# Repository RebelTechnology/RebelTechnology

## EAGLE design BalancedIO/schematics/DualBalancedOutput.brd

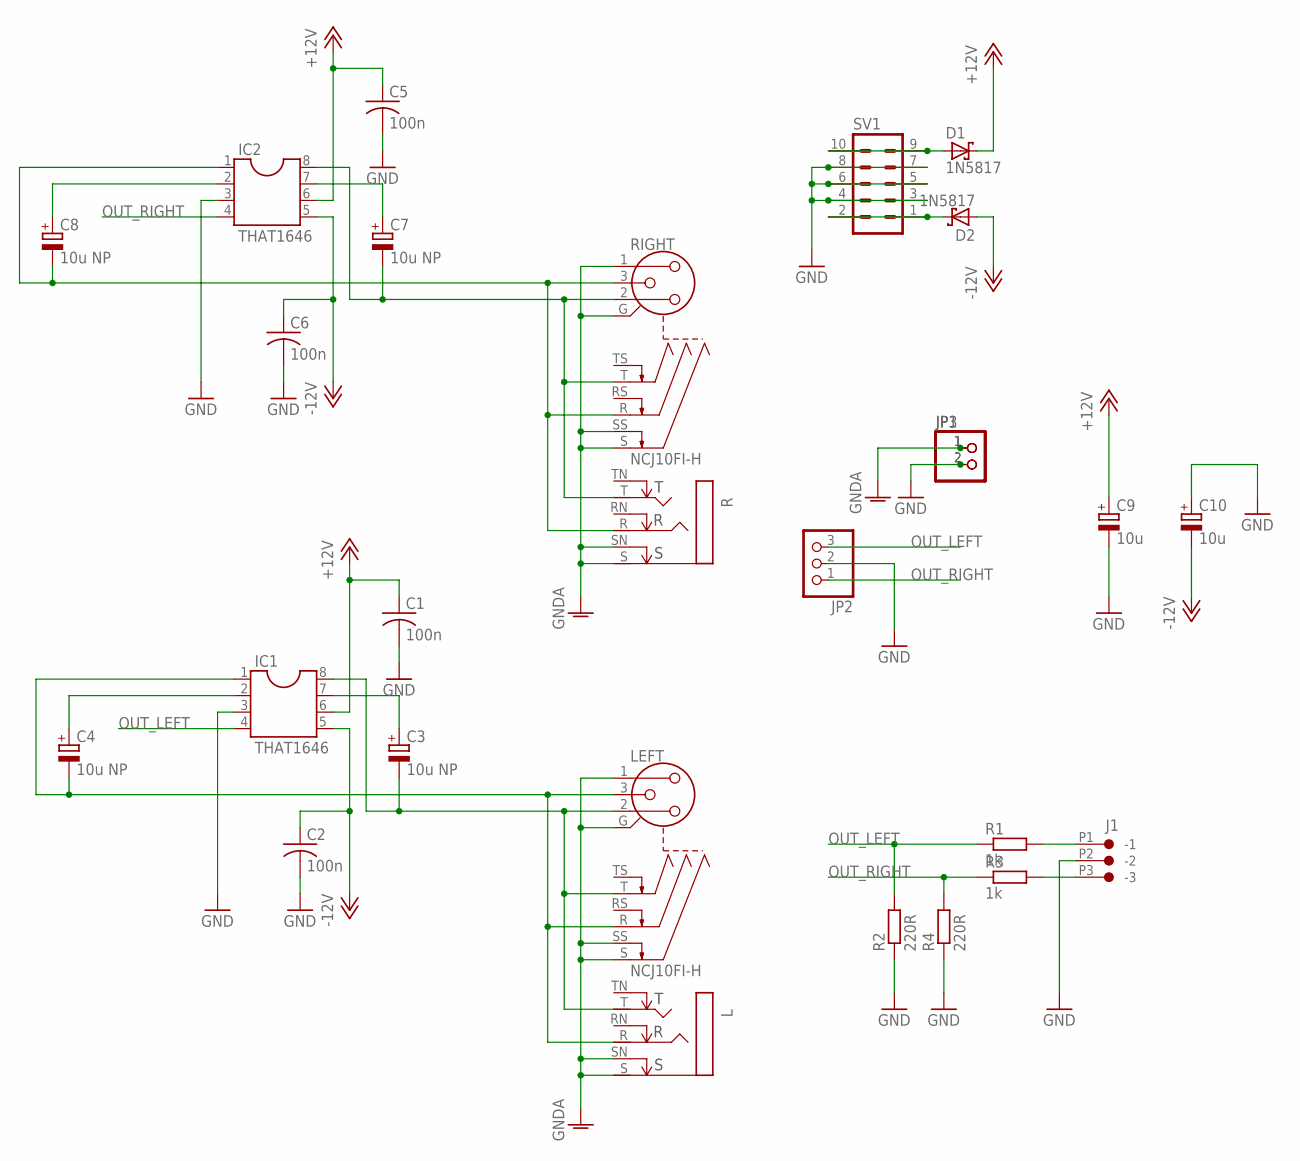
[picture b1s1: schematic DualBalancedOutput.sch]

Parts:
C1, C2, C5, C6: 100n; C050-024X044
C3, C4, C7, C8: 10u NP; E2-5
C9, C10: 10u; E5-6
D1, D2: 1N5817; DO41-7.6
IC1, IC2: THAT1646; DIL08
J1: CON-JST_PH_3W
JP1, JP3: PINHD-1X2; 1X02
JP2: PINHD-1X3; 1X03
L: NEUTRIK_NMJ6HCD2; NMJ6HCD2
LEFT: NCJ10FI-H
R: NEUTRIK_NMJ6HCD2; NMJ6HCD2
R1, R3: 1k; 0204/7
R2, R4: 220R; 0204/7
RIGHT: NCJ10FI-H
SV1: MA05-2

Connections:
+12V: C1.1, C5.1, C9.+, D1.C, IC1.6, IC2.6
-12V: C2.1, C6.1, C10.-, D2.A, IC1.5, IC2.5
GND: C1.2, C2.2, C5.2, C6.2, C9.-, C10.+, IC1.3, IC2.3, J1.P2 (-2), JP1.2, JP2.2, JP3.2, R2.1, R4.1, SV1.3, SV1.4, SV1.5, SV1.6, SV1.7, SV1.8
GNDA: JP1.1, JP3.1, L.S, L.SN, LEFT.1, LEFT.G, LEFT.S, LEFT.SS, R.S, R.SN, RIGHT.1, RIGHT.G, RIGHT.S, RIGHT.SS
unnamed: C3.-, IC1.8, L.T, LEFT.2, LEFT.T
unnamed: C4.-, IC1.1, L.R, LEFT.3, LEFT.R
unnamed: C3.+, IC1.7
unnamed: C4.+, IC1.2
unnamed: D2.C, SV1.1, SV1.2
unnamed: D1.A, SV1.9, SV1.10
unnamed: J1.P3 (-3), R3.2
unnamed: C7.+, IC2.7
unnamed: J1.P1 (-1), R1.2
unnamed: C8.+, IC2.2
unnamed: C7.-, IC2.8, R.T, RIGHT.2, RIGHT.T
unnamed: C8.-, IC2.1, R.R, RIGHT.3, RIGHT.R
OUT_LEFT: IC1.4, JP2.3, R1.1, R2.2
OUT_RIGHT: IC2.4, JP2.1, R3.1, R4.2

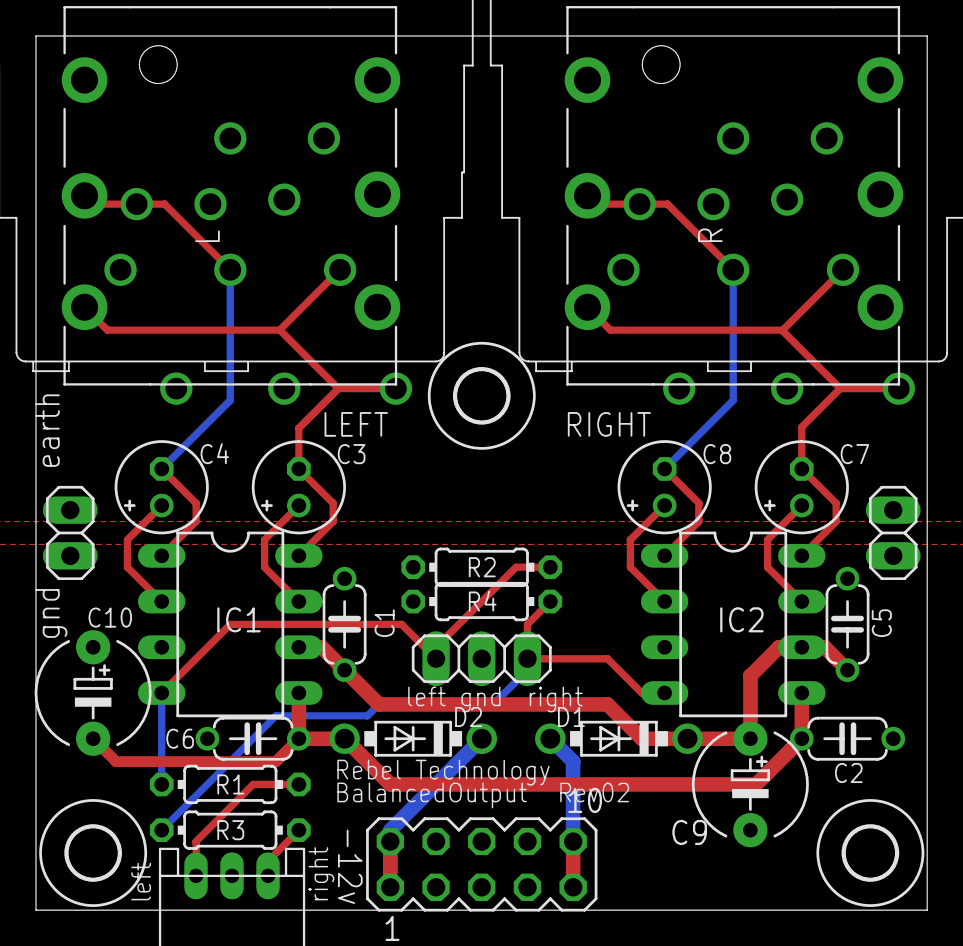
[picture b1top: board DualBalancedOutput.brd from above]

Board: 2 copper layers, 49.5 x 48.6 mm, 30 parts (0 on the bottom side), 18 nets.

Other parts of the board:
U$1, U$2, U$3: 2,8

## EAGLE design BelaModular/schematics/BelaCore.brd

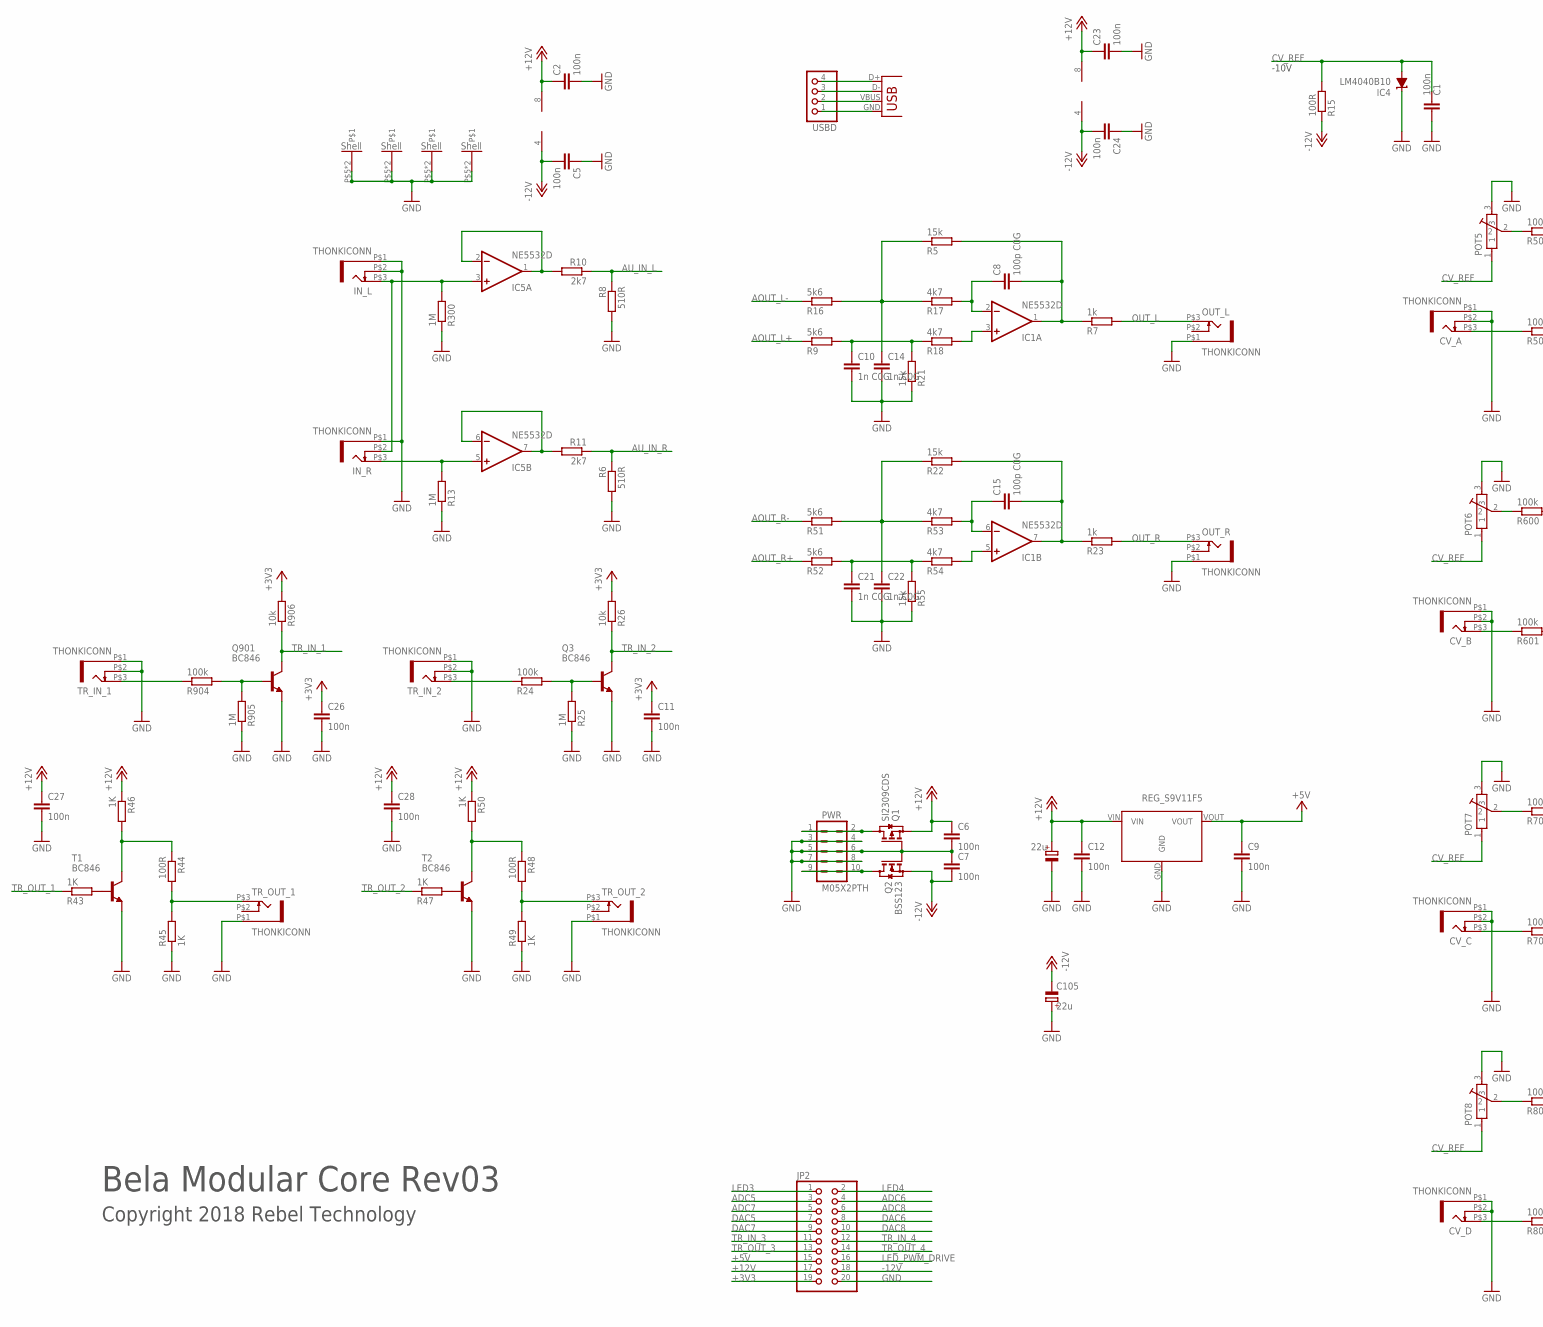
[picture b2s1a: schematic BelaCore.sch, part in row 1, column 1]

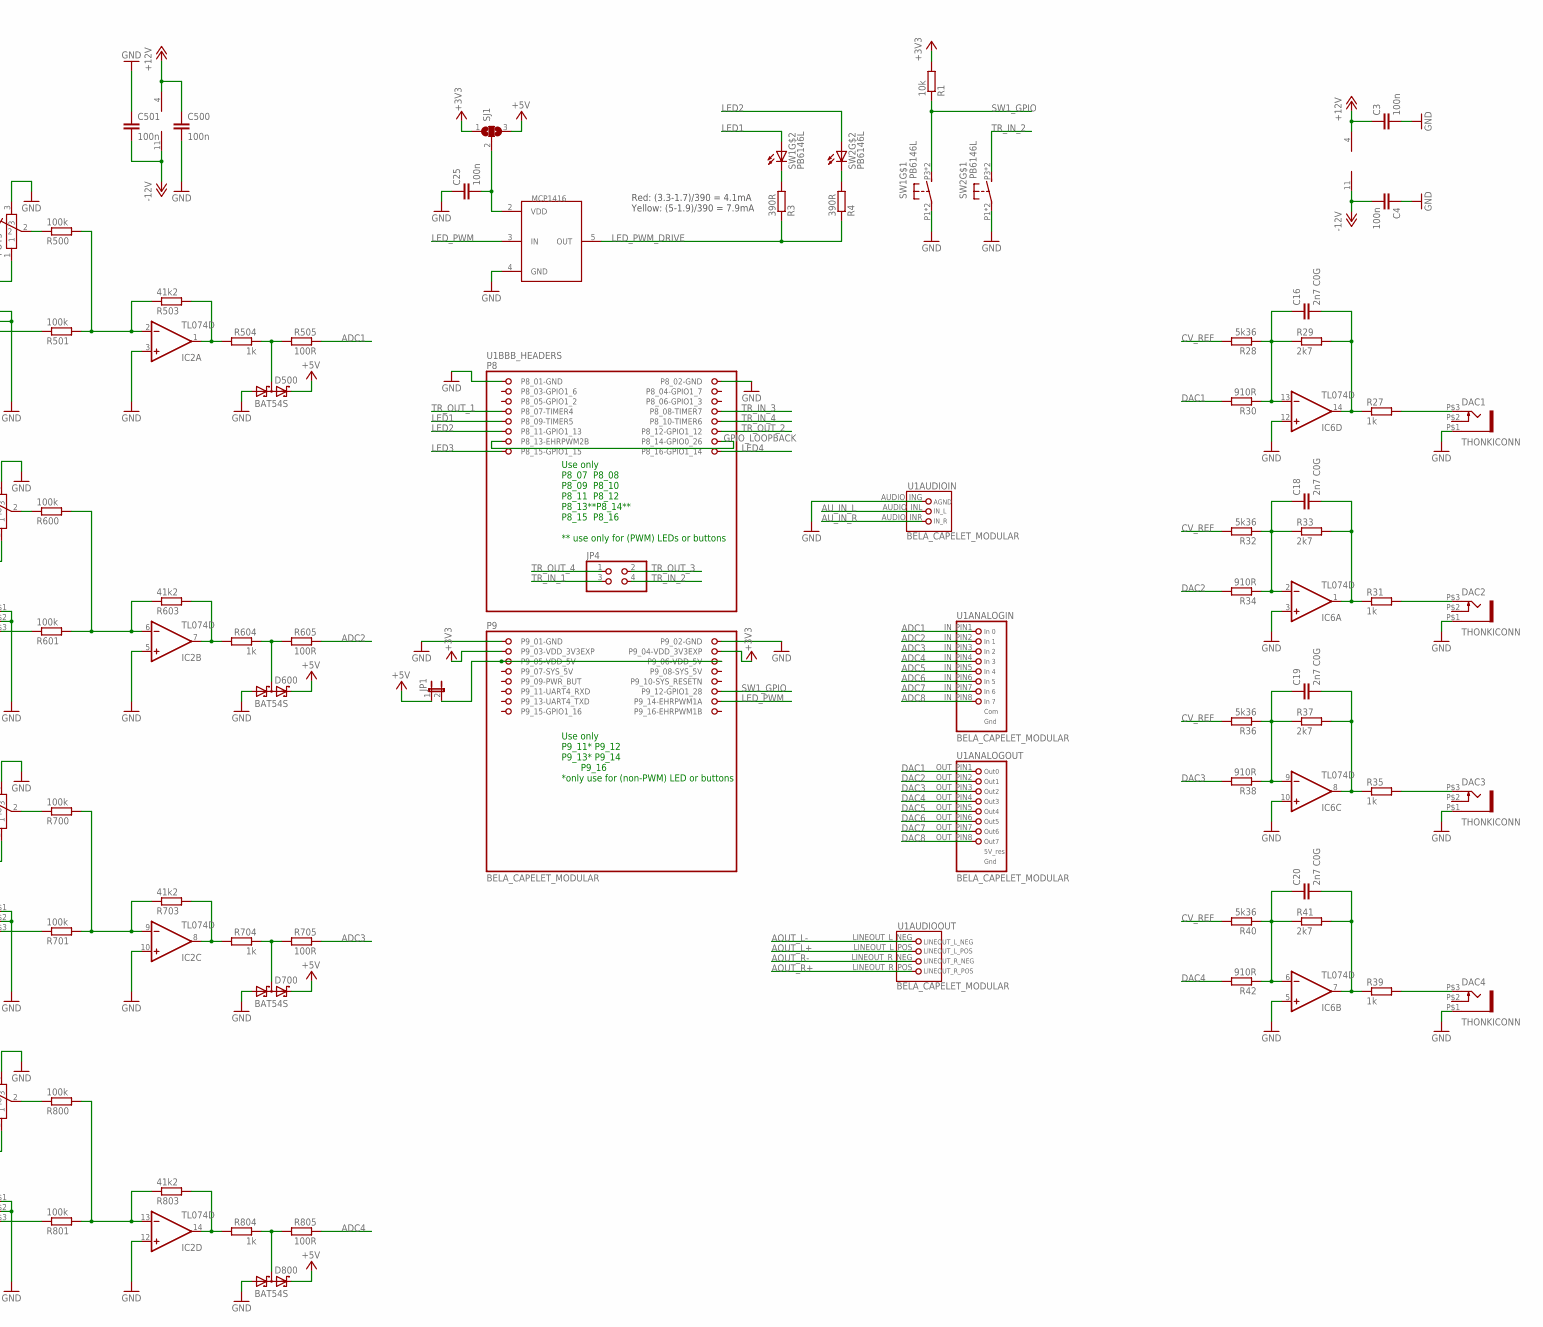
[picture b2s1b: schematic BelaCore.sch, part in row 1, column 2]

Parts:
C1, C2, C3, C4, C5, C6, C7, C9, C11, C12, C23, C24, C25, C26, C27, C28, C500, C501: 100n; C0603
C8, C15: 100p C0G; C0603
C10, C14, C21, C22: 1n C0G; C0603
C16, C18, C19, C20: 2n7 C0G; C0603
C17, C105: 22u; CPOL-5
CV_A: THONKICONN
CV_B: THONKICONN
CV_C: THONKICONN
CV_D: THONKICONN
D500, D600, D700, D800: BAT54S; SOT23
DAC1, DAC2, DAC3, DAC4: THONKICONN
IC1, IC5: NE5532D; SO08
IC2, IC6: TL074D; SO14
IC4: LM4040B10; DBZ_R-PDSO-G3
IN_L: THONKICONN
IN_R: THONKICONN
JP1: JUMPER-2PTH; 1X02
JP2: PINHD-2X10; 2X10
JP4: PINHD-2X02_2.54-SMD; 2X02SMD
OUT_L: THONKICONN
OUT_R: THONKICONN
POT5, POT6, POT7, POT8: POT-ALPS-RK09L1140
PWR: M05X2PTH; AVR_ICSP
Q1: SI2309CDS; SOT23
Q2: BSS123; SOT23
Q3, Q901: BC846; SOT23
R1, R26, R906: 10k; 0603
R3, R4: 390R; 0603
R5, R21, R22, R55: 15k; 0603
R6, R8: 510R; 0603
R7, R23, R27, R31, R35, R39, R504, R604, R704, R804: 1k; 0603
R9, R16, R51, R52: 5k6; 0603
R10, R11, R29, R33, R37, R41: 2k7; 0603
R13, R25, R300, R905: 1M; 0603
R15, R44, R48, R505, R605, R705, R805: 100R; 0603
R17, R18, R53, R54: 4k7; 0603
R24, R500, R501, R600, R601, R700, R701, R800, R801, R904: 100k; 0603
R28, R32, R36, R40: 5k36; 0603
R30, R34, R38, R42: 910R; 0603
R43, R45, R46, R47, R49, R50: 1K; 0603
R503, R603, R703, R803: 41k2; 0603
SJ1: SJ2W; SJ_2
SW1, SW2: PB6146L
T1, T2: BC846; SOT23
TR_IN_1, TR_IN_2: THONKICONN
TR_OUT_1, TR_OUT_2: THONKICONN
U1: BELA_CAPELET_MODULAR
U2: MCP1416; SOT23-5
U3: REG_S9V11F5
USBD: PINHD-1X4; 1X04
X1: USBPTH-VERTICAL; USB-B-PTH-VERTICAL

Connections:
+3V3: C11.1, C26.1, JP2.19, R1.2, R26.2, R906.2, SJ1.1, U1.P9_03 (P9_03-VDD_3V3EXP), U1.P9_04 (P9_04-VDD_3V3EXP)
+5V: C9.1, D500.2 (C2), D600.2 (C2), D700.2 (C2), D800.2 (C2), JP1.1, JP2.15, SJ1.3, U3.VOUT
+12V: C2.1, C3.1, C6.1, C12.1, C17.+, C23.1, C27.1, C28.1, C500.1, IC1.8 (V+), IC2.4 (V+), IC5.8 (V+), IC6.4 (V+), JP2.17, Q1.2 (S), R46.1, R50.1, U3.VIN
-12V: C4.2, C5.2, C7.2, C24.2, C105.-, C501.2, IC1.4 (V-), IC2.11 (V-), IC5.4 (V-), IC6.11 (V-), JP2.18, Q2.2 (S), R15.1
ADC1: R505.1, U1.IN_PIN1 (1)
ADC2: R605.1, U1.IN_PIN2 (2)
ADC3: R705.1, U1.IN_PIN3 (3)
ADC4: R805.1, U1.IN_PIN4 (4)
ADC5: JP2.3, U1.IN_PIN5 (5)
ADC6: JP2.4, U1.IN_PIN6 (6)
ADC7: JP2.5, U1.IN_PIN7 (7)
ADC8: JP2.6, U1.IN_PIN8 (8)
AOUT_L+: R9.1, U1.LINEOUT_L_POS (2)
AOUT_L-: R16.1, U1.LINEOUT_L_NEG (1)
AOUT_R+: R52.1, U1.LINEOUT_R_POS (4)
AOUT_R-: R51.1, U1.LINEOUT_R_NEG (3)
AU_IN_L: R8.1, R10.1, U1.AUDIO_INL (2)
AU_IN_R: R6.1, R11.1, U1.AUDIO_INR (3)
CV_REF: C1.1, IC4.2 (A), POT5.1, POT6.1, POT7.1, POT8.1, R15.2, R28.2, R32.2, R36.2, R40.2
DAC1: R30.2, U1.OUT_PIN1 (1)
DAC2: R34.2, U1.OUT_PIN2 (2)
DAC3: R38.2, U1.OUT_PIN3 (3)
DAC4: R42.2, U1.OUT_PIN4 (4)
DAC5: JP2.7, U1.OUT_PIN5 (5)
DAC6: JP2.8, U1.OUT_PIN6 (6)
DAC7: JP2.9, U1.OUT_PIN7 (7)
DAC8: JP2.10, U1.OUT_PIN8 (8)
GND: C1.2, C2.2, C3.2, C4.1, C5.1, C6.2, C7.1, C9.2, C10.2, C11.2, C12.2, C14.2, C17.-, C21.2, C22.2, C23.2, C24.1, C25.1, C26.2, C27.2, C28.2, C105.+, C500.2, C501.1, CV_A.P$1 (5), CV_A.P$2 (4), CV_B.P$1 (5), CV_B.P$2 (4), CV_C.P$1 (5), CV_C.P$2 (4), CV_D.P$1 (5), CV_D.P$2 (4), D500.1 (A1), D600.1 (A1), D700.1 (A1), D800.1 (A1), DAC1.P$1 (5), DAC2.P$1 (5), DAC3.P$1 (5), DAC4.P$1 (5), IC2.3 (+IN), IC2.5 (+IN), IC2.10 (+IN), IC2.12 (+IN), IC4.1 (C), IC6.3 (+IN), IC6.5 (+IN), IC6.10 (+IN), IC6.12 (+IN), IN_L.P$1 (5), IN_L.P$2 (4), IN_R.P$1 (5), JP2.20, OUT_L.P$1 (5), OUT_R.P$1 (5), POT5.3, POT5.P$5, POT5.P$6, POT6.3, POT6.P$5, POT6.P$6, POT7.3, POT7.P$5, POT7.P$6, POT8.3, POT8.P$5, POT8.P$6, PWR.3, PWR.4, PWR.5, PWR.6, PWR.7, PWR.8, Q1.1 (G), Q2.1 (G), Q3.2 (E), Q901.2 (E), R6.2, R8.2, R13.1, R21.1, R25.1, R45.1, R49.1, R55.1, R300.1, R905.1, SW1.P1, SW1.P2, SW2.P1, SW2.P2, T1.2 (E), T2.2 (E), TR_IN_1.P$1 (5), TR_IN_1.P$2 (4), TR_IN_2.P$1 (5), TR_IN_2.P$2 (4), TR_OUT_1.P$1 (5), TR_OUT_2.P$1 (5), U1.AUDIO_ING (1), U1.P8_01 (P8_01-GND), U1.P8_02 (P8_02-GND), U1.P9_01 (P9_01-GND), U1.P9_02 (P9_02-GND), U2.4 (GND), U3.GND
GPIO_LOOPBACK: U1.P8_13 (P8_13-EHRPWM2B), U1.P8_14 (P8_14-GPIO0_26)
IN_L: IC5.3 (+IN), IN_L.P$3 (3), IN_R.P$2 (4), R300.2
LED1: SW1.PL1 (A), U1.P8_09 (P8_09-TIMER5)
LED2: SW2.PL1 (A), U1.P8_11 (P8_11-GPIO1_13)
LED3: JP2.1, U1.P8_15 (P8_15-GPIO1_15)
LED4: JP2.2, U1.P8_16 (P8_16-GPIO1_14)
LED_PWM: U1.P9_14 (P9_14-EHRPWM1A), U2.3 (IN)
LED_PWM_DRIVE: JP2.16, R3.1, R4.1, U2.5 (OUT)
unnamed: IC5.6 (-IN), IC5.7 (OUT), R11.2
unnamed: IC5.1 (OUT), IC5.2 (-IN), R10.2
unnamed: CV_A.P$3 (3), R501.1
unnamed: JP1.2, U1.P9_05 (P9_05-VDD_5V), U1.P9_06 (P9_06-VDD_5V)
unnamed: R3.2, SW1.PL2 (C)
unnamed: IC2.9 (-IN), R700.2, R701.2, R703.1
unnamed: C25.2, SJ1.2, U2.2 (VDD)
unnamed: PWR.9, PWR.10, Q2.3 (D)
unnamed: R4.2, SW2.PL2 (C)
unnamed: C8.2, IC1.1 (OUT), R5.2, R7.1
unnamed: C8.1, IC1.2 (-IN), R17.2
unnamed: PWR.1, PWR.2, Q1.3 (D)
unnamed: IC2.2 (-IN), R500.2, R501.2, R503.1
unnamed: POT5.2, R500.1
unnamed: IC1.3 (+IN), R18.2
unnamed: D500.3 (C1A2), R504.1, R505.2
unnamed: IC2.1 (OUT), R503.2, R504.2
unnamed: CV_B.P$3 (3), R601.1
unnamed: IC2.6 (-IN), R600.2, R601.2, R603.1
unnamed: POT6.2, R600.1
unnamed: IC2.7 (OUT), R603.2, R604.2
unnamed: D600.3 (C1A2), R604.1, R605.2
unnamed: C10.1, R9.2, R18.1, R21.2
unnamed: CV_C.P$3 (3), R701.1
unnamed: POT7.2, R700.1
unnamed: IC2.8 (OUT), R703.2, R704.2
unnamed: D700.3 (C1A2), R704.1, R705.2
unnamed: C15.2, IC1.7 (OUT), R22.2, R23.1
unnamed: CV_D.P$3 (3), R801.1
unnamed: C22.1, R22.1, R51.2, R53.1
unnamed: IC2.13 (-IN), R800.2, R801.2, R803.1
unnamed: POT8.2, R800.1
unnamed: IC2.14 (OUT), R803.2, R804.2
unnamed: D800.3 (C1A2), R804.1, R805.2
unnamed: Q901.1 (B), R904.2, R905.2
unnamed: R43.2, T1.1 (B)
unnamed: C15.1, IC1.6 (-IN), R53.2
unnamed: C14.1, R5.1, R16.2, R17.1
unnamed: IC1.5 (+IN), R54.2
unnamed: C21.1, R52.2, R54.1, R55.2
unnamed: R44.1, R46.2, T1.3 (C)
unnamed: Q3.1 (B), R24.2, R25.2
unnamed: R904.1, TR_IN_1.P$3 (3)
unnamed: R24.1, TR_IN_2.P$3 (3)
unnamed: IC5.5 (+IN), IN_R.P$3 (3), R13.2
unnamed: C16.2, IC6.14 (OUT), R27.1, R29.2
unnamed: C16.1, IC6.13 (-IN), R28.1, R29.1, R30.1
unnamed: DAC1.P$3 (3), R27.2
unnamed: C18.2, IC6.1 (OUT), R31.1, R33.2
unnamed: C18.1, IC6.2 (-IN), R32.1, R33.1, R34.1
unnamed: DAC2.P$3 (3), R31.2
unnamed: C19.2, IC6.8 (OUT), R35.1, R37.2
unnamed: C19.1, IC6.9 (-IN), R36.1, R37.1, R38.1
unnamed: DAC3.P$3 (3), R35.2
unnamed: C20.2, IC6.7 (OUT), R39.1, R41.2
unnamed: C20.1, IC6.6 (-IN), R40.1, R41.1, R42.1
unnamed: DAC4.P$3 (3), R39.2
unnamed: R44.2, R45.2, TR_OUT_1.P$3 (3)
unnamed: R47.2, T2.1 (B)
unnamed: R48.1, R50.2, T2.3 (C)
unnamed: R48.2, R49.2, TR_OUT_2.P$3 (3)
unnamed: USBD.4, X1.D+
unnamed: USBD.1, X1.GND
unnamed: USBD.2, X1.VBUS
unnamed: USBD.3, X1.D-
OUT_L: OUT_L.P$3 (3), R7.2
OUT_R: OUT_R.P$3 (3), R23.2
P9_07-SYS_5V: U1.P9_07 (P9_07-SYS_5V)
SW1_GPIO: R1.1, SW1.P3 (S), SW1.P4 (S), U1.P9_12 (P9_12-GPIO1_28)
TR_IN_1: JP4.3, Q901.3 (C), R906.1
TR_IN_2: JP4.4, Q3.3 (C), R26.1, SW2.P3 (S), SW2.P4 (S)
TR_IN_3: JP2.11, U1.P8_08 (P8_08-TIMER7)
TR_IN_4: JP2.12, U1.P8_10 (P8_10-TIMER6)
TR_OUT_1: R43.1, U1.P8_07 (P8_07-TIMER4)
TR_OUT_2: R47.1, U1.P8_12 (P8_12-GPIO1_12)
TR_OUT_3: JP2.13, JP4.2
TR_OUT_4: JP2.14, JP4.1

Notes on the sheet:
Bela Modular Core Rev03
Copyright 2018 Rebel Technology
-10V
Use only P8_07 P8_08 P8_09 P8_10 P8_11 P8_12 P8_13**P8_14** P8_15 P8_16 ** use only for (PWM) LEDs or buttons
Use only P9_11* P9_12 P9_13* P9_14 P9_16 *only use for (non-PWM) LED or buttons
Red: (3.3-1.7)/390 = 4.1mA Yellow: (5-1.9)/390 = 7.9mA

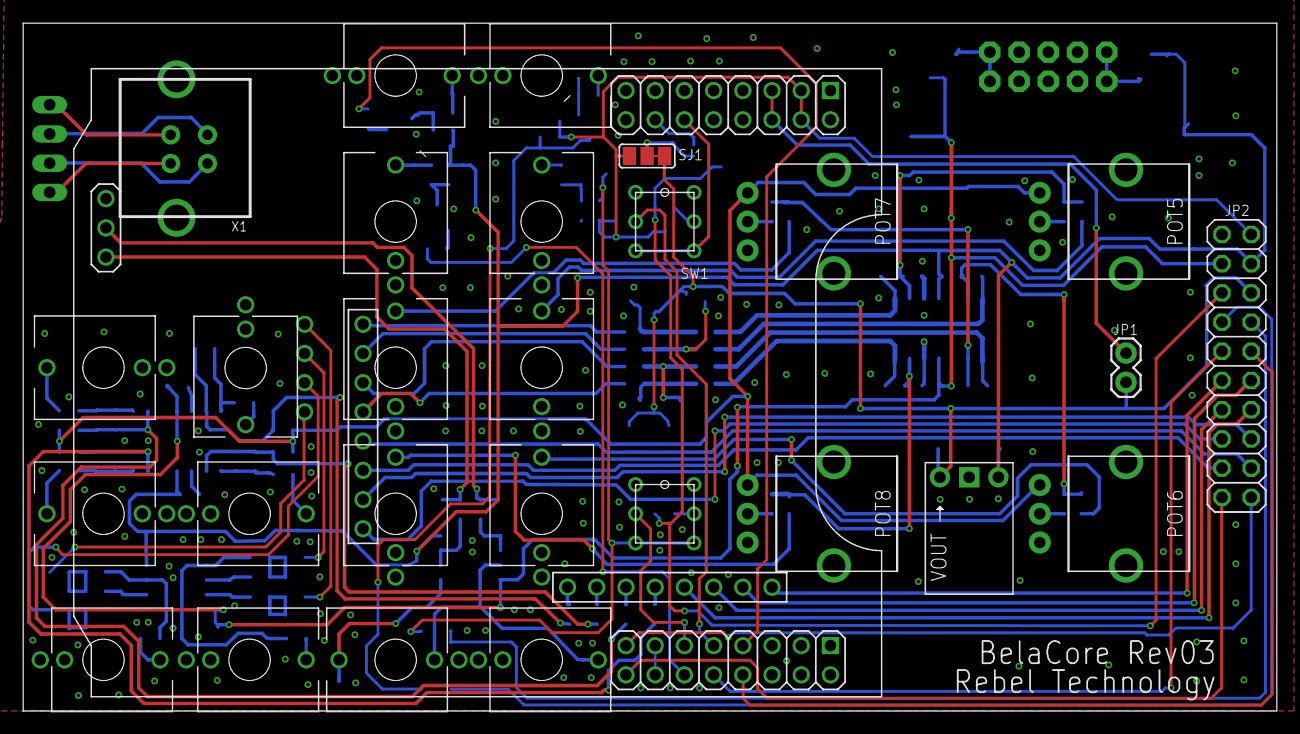
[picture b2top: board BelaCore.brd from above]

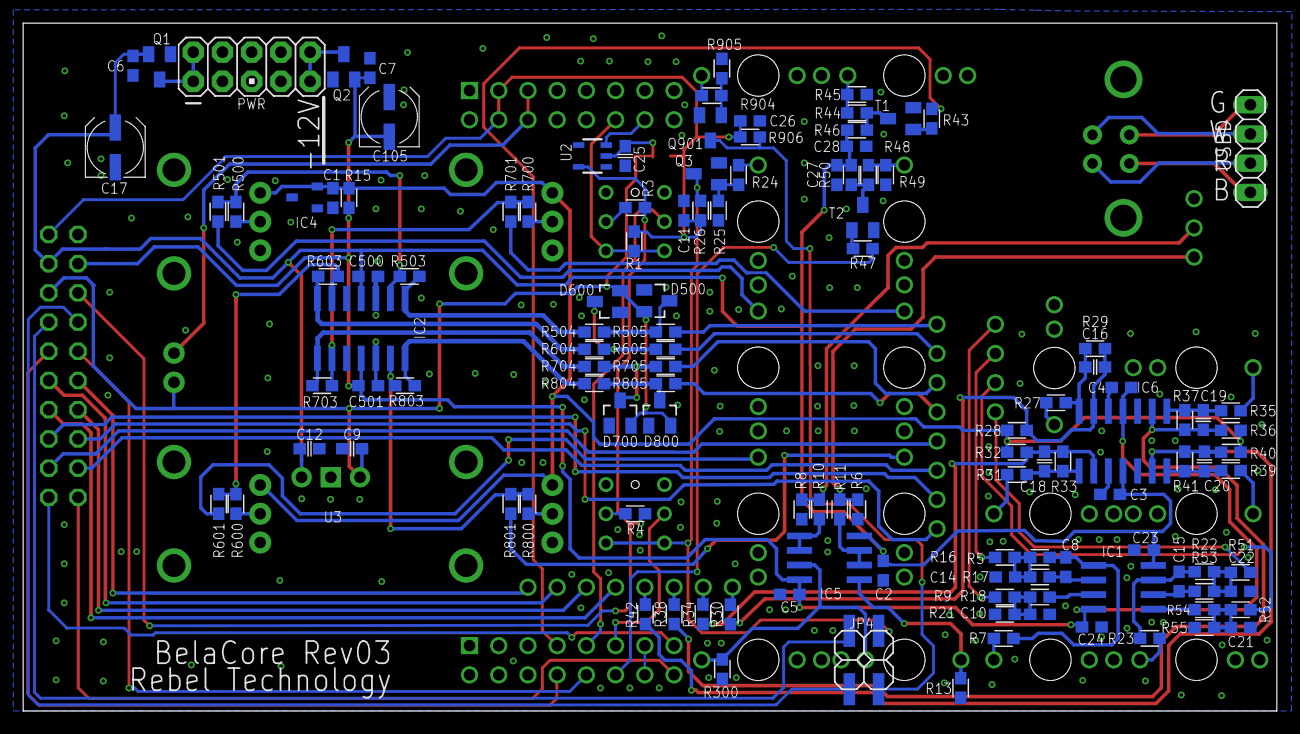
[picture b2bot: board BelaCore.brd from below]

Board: 2 copper layers, 109.0 x 59.8 mm, 151 parts (123 on the bottom side), 112 nets.

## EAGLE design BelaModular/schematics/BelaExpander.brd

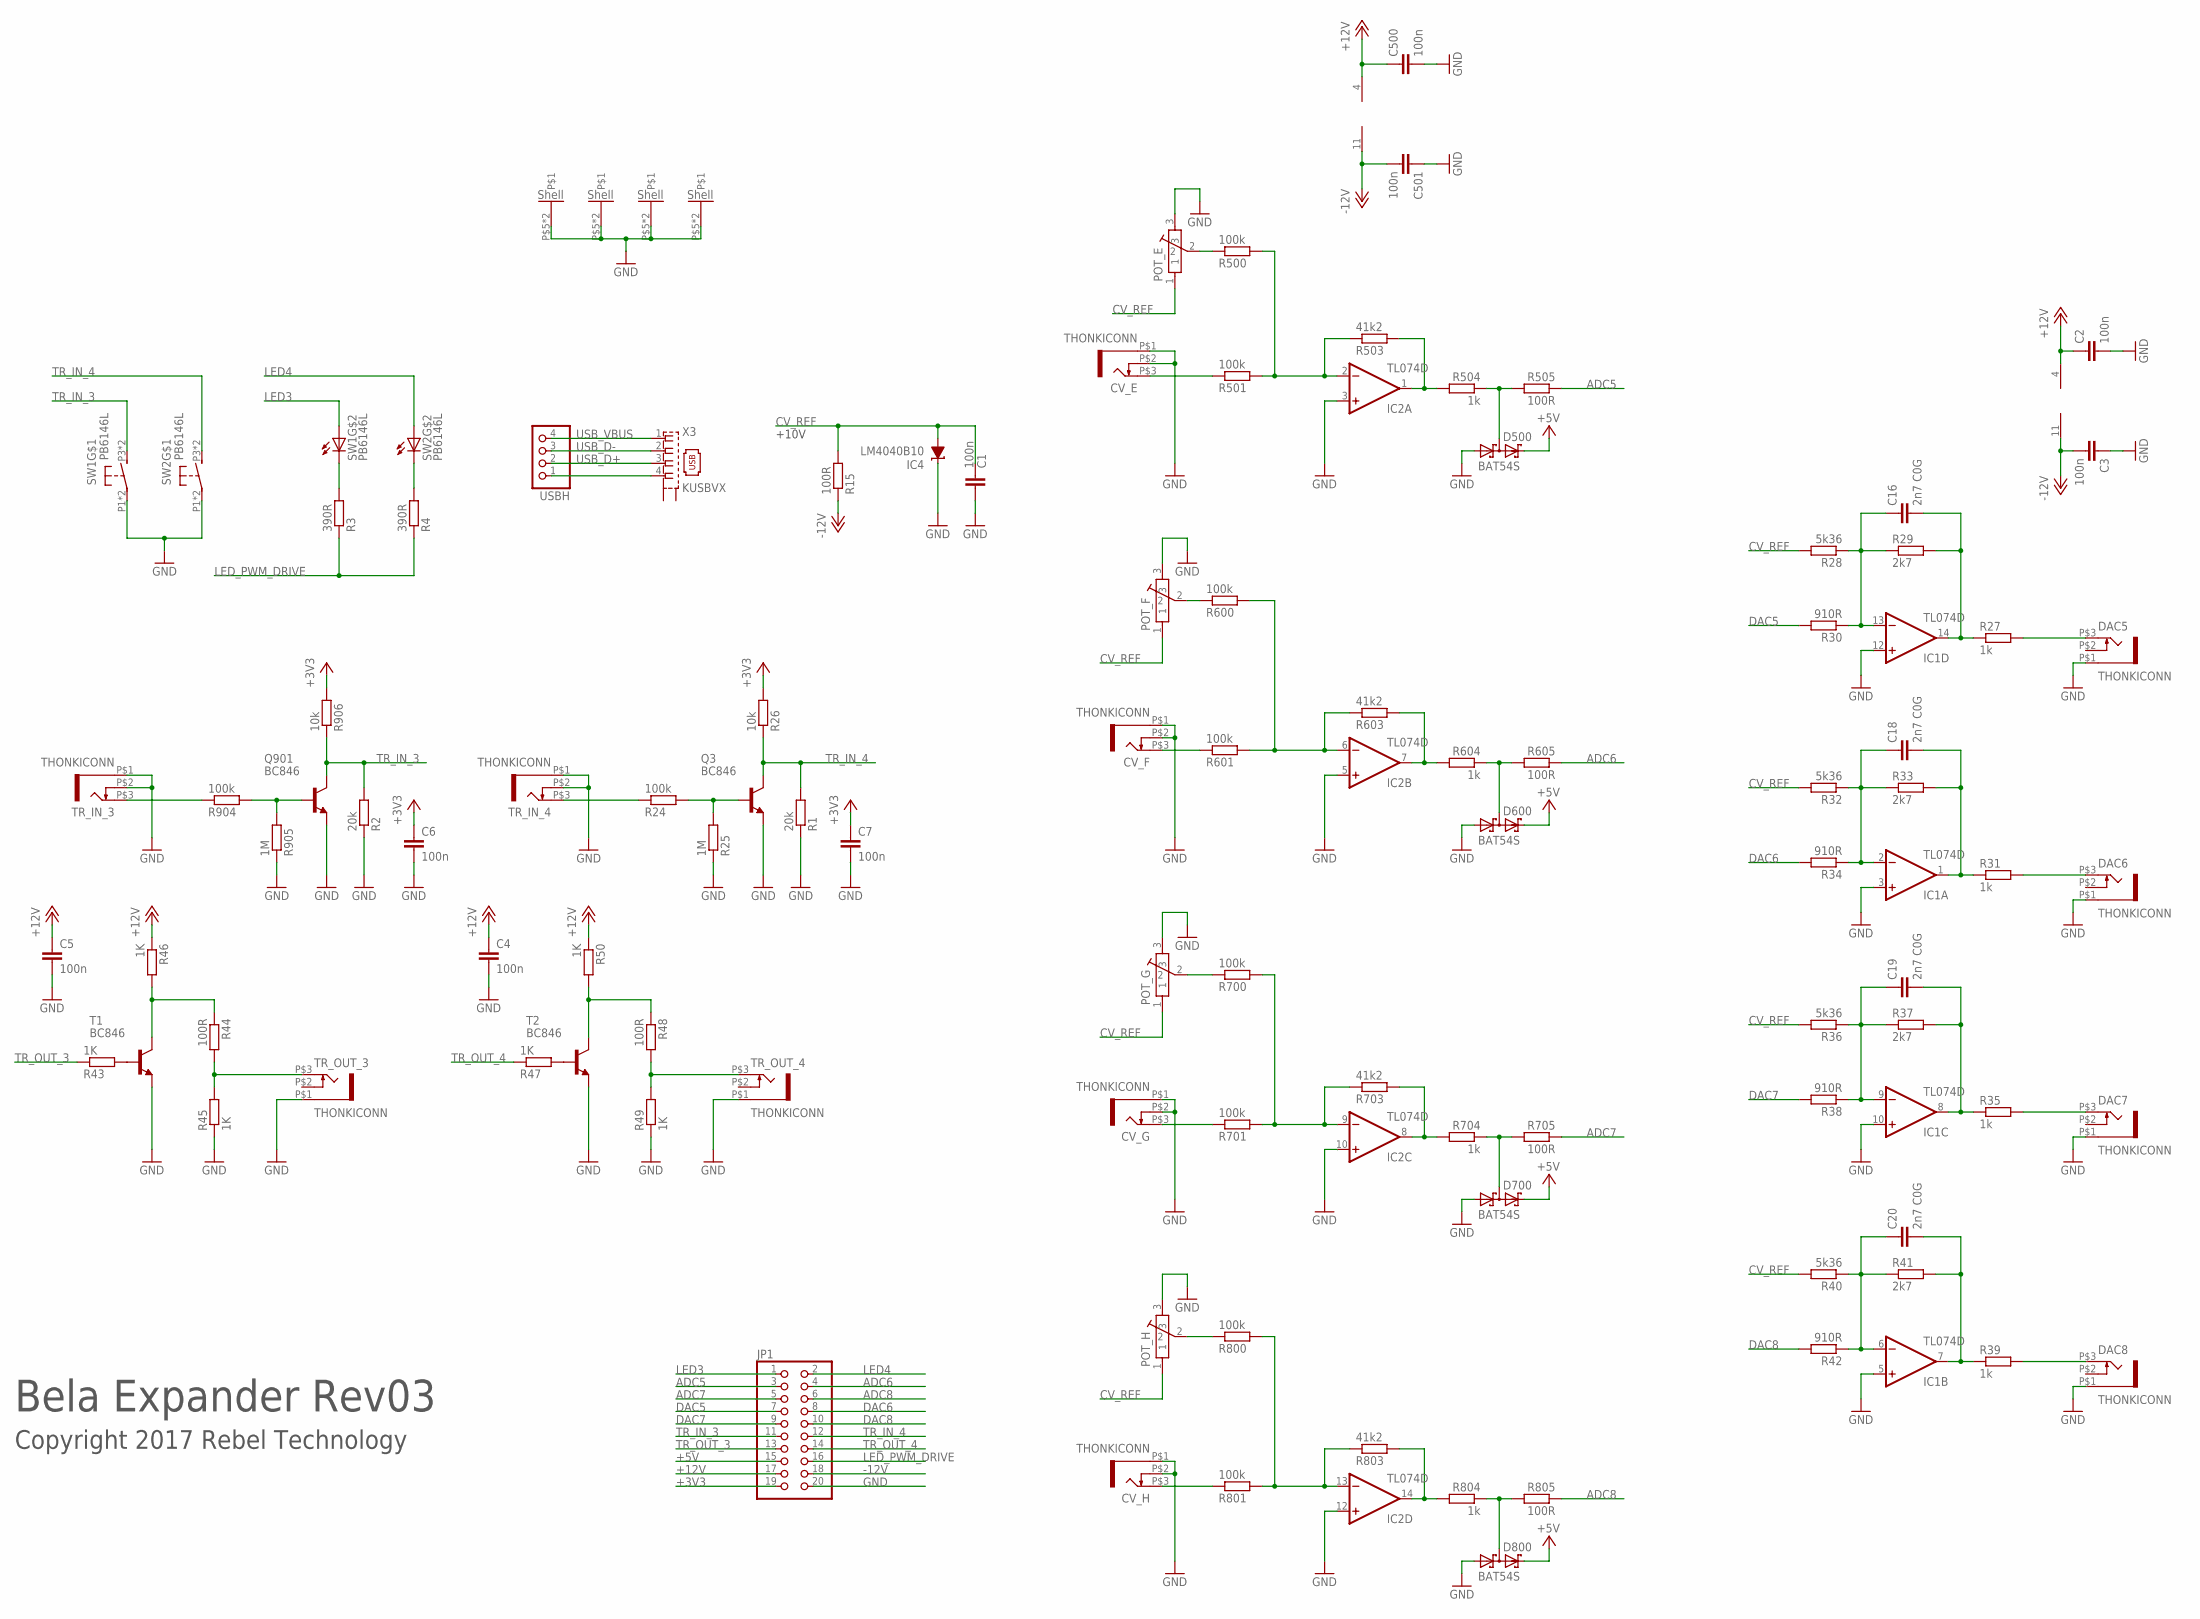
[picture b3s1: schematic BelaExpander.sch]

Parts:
C1, C2, C3, C4, C5, C6, C7, C500, C501: 100n; C0603
C16, C18, C19, C20: 2n7 C0G; C0603
CV_E: THONKICONN
CV_F: THONKICONN
CV_G: THONKICONN
CV_H: THONKICONN
D500, D600, D700, D800: BAT54S; SOT23
DAC5, DAC6, DAC7, DAC8: THONKICONN
IC1, IC2: TL074D; SO14
IC4: LM4040B10; DBZ_R-PDSO-G3
JP1: PINHD-2X10; 2X10
POT_E: POT-ALPS-RK09L1140
POT_F: POT-ALPS-RK09L1140
POT_G: POT-ALPS-RK09L1140
POT_H: POT-ALPS-RK09L1140
Q3, Q901: BC846; SOT23
R1, R2: 20k; 0603
R3, R4: 390R; 0603
R15, R44, R48, R505, R605, R705, R805: 100R; 0603
R24, R500, R501, R600, R601, R700, R701, R800, R801, R904: 100k; 0603
R25, R905: 1M; 0603
R26, R906: 10k; 0603
R27, R31, R35, R39, R504, R604, R704, R804: 1k; 0603
R28, R32, R36, R40: 5k36; 0603
R29, R33, R37, R41: 2k7; 0603
R30, R34, R38, R42: 910R; 0603
R43, R45, R46, R47, R49, R50: 1K; 0603
R503, R603, R703, R803: 41k2; 0603
SW1, SW2: PB6146L
T1, T2: BC846; SOT23
TR_IN_3, TR_IN_4: THONKICONN
TR_OUT_3, TR_OUT_4: THONKICONN
USBH: PINHD-1X4; 1X04
X3: KUSBVX

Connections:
+3V3: C6.1, C7.1, JP1.19, R26.2, R906.2
+5V: D500.2 (C2), D600.2 (C2), D700.2 (C2), D800.2 (C2), JP1.15
+12V: C2.1, C4.1, C5.1, C500.1, IC1.4 (V+), IC2.4 (V+), JP1.17, R46.1, R50.1
-12V: C3.2, C501.2, IC1.11 (V-), IC2.11 (V-), JP1.18, R15.1
ADC5: JP1.3, R505.1
ADC6: JP1.4, R605.1
ADC7: JP1.5, R705.1
ADC8: JP1.6, R805.1
CV_REF: C1.1, IC4.2 (A), POT_E.1, POT_F.1, POT_G.1, POT_H.1, R15.2, R28.2, R32.2, R36.2, R40.2
DAC5: JP1.7, R30.2
DAC6: JP1.8, R34.2
DAC7: JP1.9, R38.2
DAC8: JP1.10, R42.2
GND: C1.2, C2.2, C3.1, C4.2, C5.2, C6.2, C7.2, C500.2, C501.1, CV_E.P$1 (5), CV_E.P$2 (4), CV_F.P$1 (5), CV_F.P$2 (4), CV_G.P$1 (5), CV_G.P$2 (4), CV_H.P$1 (5), CV_H.P$2 (4), D500.1 (A1), D600.1 (A1), D700.1 (A1), D800.1 (A1), DAC5.P$1 (5), DAC6.P$1 (5), DAC7.P$1 (5), DAC8.P$1 (5), IC1.3 (+IN), IC1.5 (+IN), IC1.10 (+IN), IC1.12 (+IN), IC2.3 (+IN), IC2.5 (+IN), IC2.10 (+IN), IC2.12 (+IN), IC4.1 (C), JP1.20, POT_E.3, POT_E.P$5, POT_E.P$6, POT_F.3, POT_F.P$5, POT_F.P$6, POT_G.3, POT_G.P$5, POT_G.P$6, POT_H.3, POT_H.P$5, POT_H.P$6, Q3.2 (E), Q901.2 (E), R1.1, R2.1, R25.1, R45.1, R49.1, R905.1, SW1.P1, SW1.P2, SW2.P1, SW2.P2, T1.2 (E), T2.2 (E), TR_IN_3.P$1 (5), TR_IN_3.P$2 (4), TR_IN_4.P$1 (5), TR_IN_4.P$2 (4), TR_OUT_3.P$1 (5), TR_OUT_4.P$1 (5)
LED3: JP1.1, SW1.PL1 (A)
LED4: JP1.2, SW2.PL1 (A)
LED_PWM_DRIVE: JP1.16, R3.1, R4.1
unnamed: USBH.1, X3.4
unnamed: CV_E.P$3 (3), R501.1
unnamed: R3.2, SW1.PL2 (C)
unnamed: IC2.9 (-IN), R700.2, R701.2, R703.1
unnamed: R4.2, SW2.PL2 (C)
unnamed: IC2.2 (-IN), R500.2, R501.2, R503.1
unnamed: POT_E.2, R500.1
unnamed: D500.3 (C1A2), R504.1, R505.2
unnamed: IC2.1 (OUT), R503.2, R504.2
unnamed: CV_F.P$3 (3), R601.1
unnamed: IC2.6 (-IN), R600.2, R601.2, R603.1
unnamed: POT_F.2, R600.1
unnamed: IC2.7 (OUT), R603.2, R604.2
unnamed: D600.3 (C1A2), R604.1, R605.2
unnamed: CV_G.P$3 (3), R701.1
unnamed: POT_G.2, R700.1
unnamed: IC2.8 (OUT), R703.2, R704.2
unnamed: D700.3 (C1A2), R704.1, R705.2
unnamed: CV_H.P$3 (3), R801.1
unnamed: IC2.13 (-IN), R800.2, R801.2, R803.1
unnamed: POT_H.2, R800.1
unnamed: IC2.14 (OUT), R803.2, R804.2
unnamed: D800.3 (C1A2), R804.1, R805.2
unnamed: Q901.1 (B), R904.2, R905.2
unnamed: R43.2, T1.1 (B)
unnamed: R44.1, R46.2, T1.3 (C)
unnamed: Q3.1 (B), R24.2, R25.2
unnamed: R904.1, TR_IN_3.P$3 (3)
unnamed: R24.1, TR_IN_4.P$3 (3)
unnamed: C16.2, IC1.14 (OUT), R27.1, R29.2
unnamed: C16.1, IC1.13 (-IN), R28.1, R29.1, R30.1
unnamed: DAC5.P$3 (3), R27.2
unnamed: C18.2, IC1.1 (OUT), R31.1, R33.2
unnamed: C18.1, IC1.2 (-IN), R32.1, R33.1, R34.1
unnamed: DAC6.P$3 (3), R31.2
unnamed: C19.2, IC1.8 (OUT), R35.1, R37.2
unnamed: C19.1, IC1.9 (-IN), R36.1, R37.1, R38.1
unnamed: DAC7.P$3 (3), R35.2
unnamed: C20.2, IC1.7 (OUT), R39.1, R41.2
unnamed: C20.1, IC1.6 (-IN), R40.1, R41.1, R42.1
unnamed: DAC8.P$3 (3), R39.2
unnamed: R44.2, R45.2, TR_OUT_3.P$3 (3)
unnamed: R47.2, T2.1 (B)
unnamed: R48.1, R50.2, T2.3 (C)
unnamed: R48.2, R49.2, TR_OUT_4.P$3 (3)
TR_IN_3: JP1.11, Q901.3 (C), R2.2, R906.1, SW1.P3 (S), SW1.P4 (S)
TR_IN_4: JP1.12, Q3.3 (C), R1.2, R26.1, SW2.P3 (S), SW2.P4 (S)
TR_OUT_3: JP1.13, R43.1
TR_OUT_4: JP1.14, R47.1
USB_D+: USBH.2, X3.3
USB_D-: USBH.3, X3.2
USB_VBUS: USBH.4, X3.1

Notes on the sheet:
Bela Expander Rev03
Copyright 2017 Rebel Technology
+10V

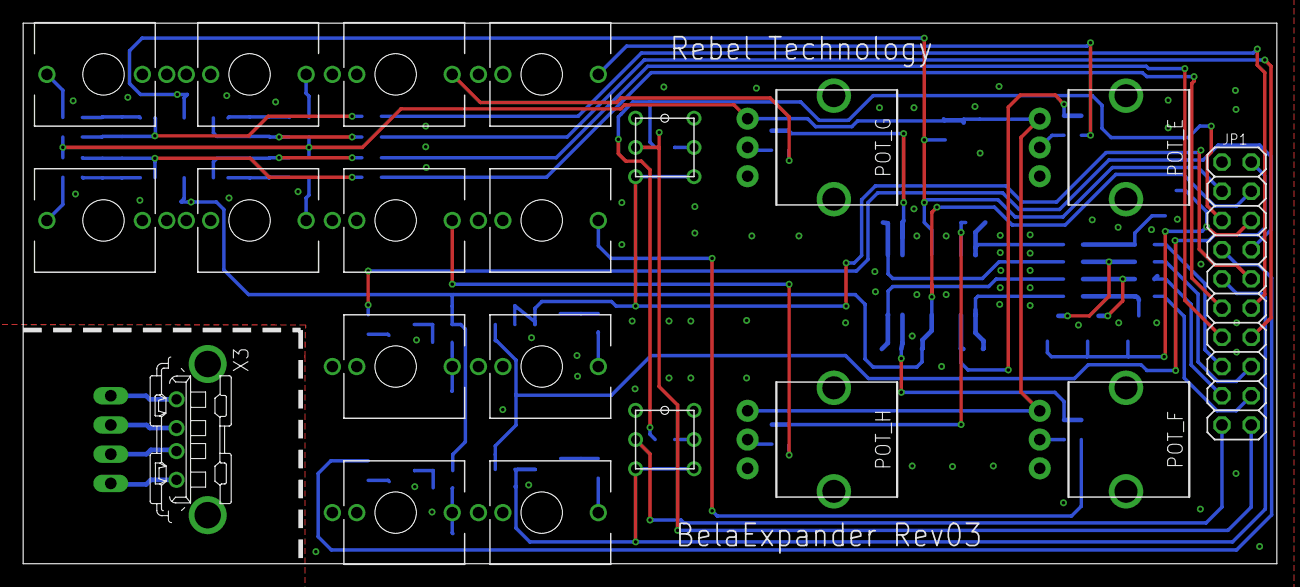
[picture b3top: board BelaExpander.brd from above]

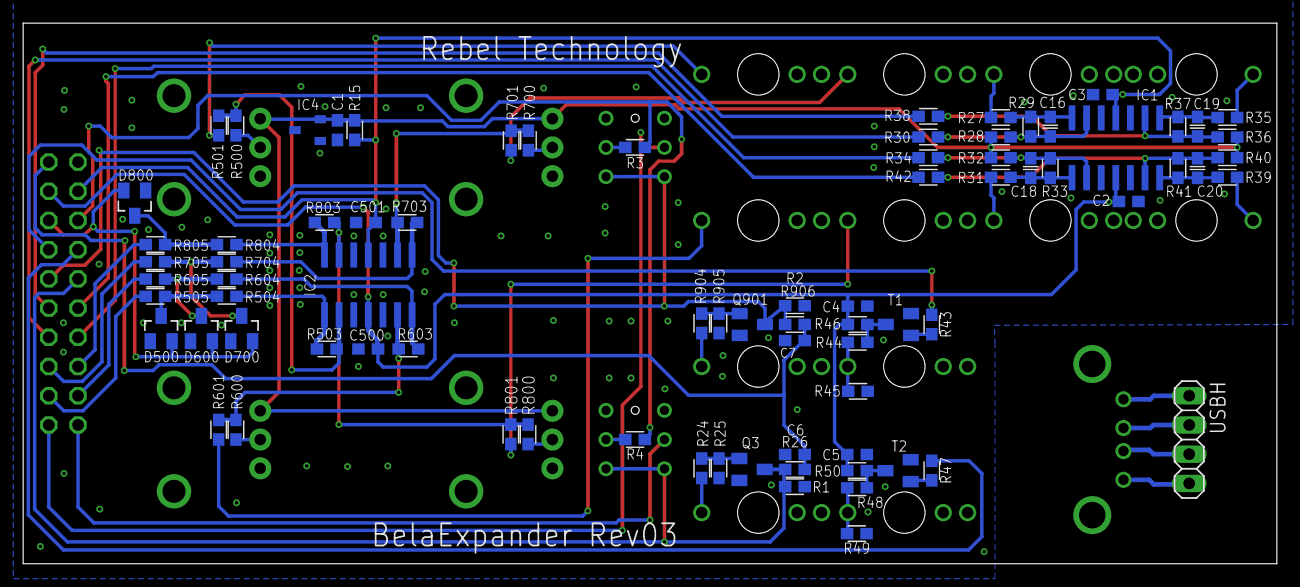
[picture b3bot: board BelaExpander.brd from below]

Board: 2 copper layers, 109.0 x 47.0 mm, 100 parts (80 on the bottom side), 69 nets.

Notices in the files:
parts and their libraries:
SparkFun: Licensing: CC v3.0 Share-Alike You are welcome to use this library for commercial purposes.
SparkFun-Retired: Licensing: Creative Commons ShareAlike 4.0 International - https://creativecommons.org/licenses/by-sa/4.0
